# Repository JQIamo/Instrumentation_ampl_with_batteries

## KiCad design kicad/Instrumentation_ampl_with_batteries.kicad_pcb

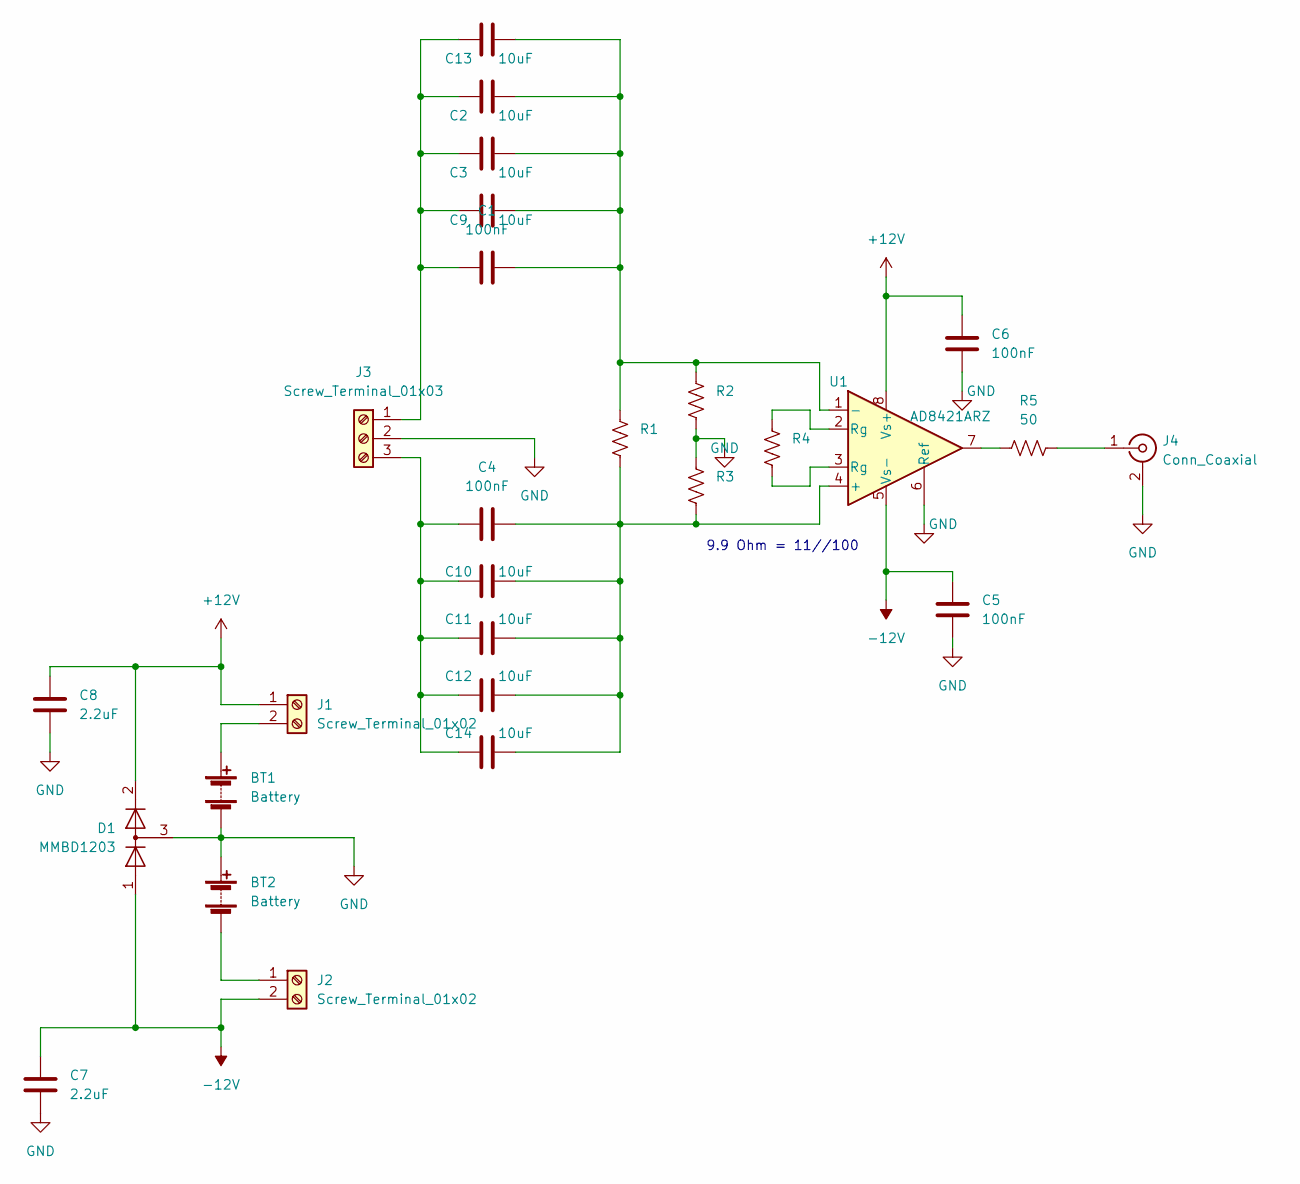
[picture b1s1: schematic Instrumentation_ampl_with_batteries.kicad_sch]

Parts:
BT1, BT2: Battery; 12V_cell_holder
C1, C4, C5, C6: 100nF; C_0603_1608Metric_Pad1.08x0.95mm_HandSolder
C2, C3, C9, C10, C11, C12, C13, C14: 10uF; C_1210_3225Metric
C7, C8: 2.2uF; C_0805_2012Metric_Pad1.18x1.45mm_HandSolder
D1: MMBD1203; SOT-23
J1, J2: Screw_Terminal_01x02; PinHeader_1x02_P2.54mm_Vertical
J3: Screw_Terminal_01x03; TerminalBlock_4Ucon_1x03_P3.50mm_Horizontal
J4: Conn_Coaxial; BNC_1cm
R1, R2, R3, R4: R_0603_1608Metric_Pad0.98x0.95mm_HandSolder
R5: 50; R_0603_1608Metric_Pad0.98x0.95mm_HandSolder
U1: AD8421ARZ; PowerIntegrations_SO-8

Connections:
+12V: C6.1, C8.1, D1.2 (A), J1.1, U1.8 (Vs+)
-12V: C5.1, C7.1, D1.1 (K), J2.2, U1.5 (Vs-)
GND: BT1.2 (-), BT2.1 (+), C5.2, C6.2, C7.2, C8.2, D1.3 (K), J3.2, J4.2 (Ext), R2.1, R3.2, U1.6 (Ref)
unnamed: BT1.1 (+), J1.2
unnamed: BT2.2 (-), J2.1
unnamed: C1.1, C2.1, C3.1, C9.1, C13.1, J3.1
unnamed: C1.2, C2.2, C3.2, C9.2, C13.2, R1.2, R2.2, U1.1 (-)
unnamed: C4.1, C10.1, C11.1, C12.1, C14.1, J3.3
unnamed: J4.1 (In), R5.2
unnamed: C4.2, C10.2, C11.2, C12.2, C14.2, R1.1, R3.1, U1.4 (+)
unnamed: R4.1, U1.3 (Rg)
unnamed: R4.2, U1.2 (Rg)
unnamed: R5.1, U1.7

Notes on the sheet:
9.9 Ohm = 11//100

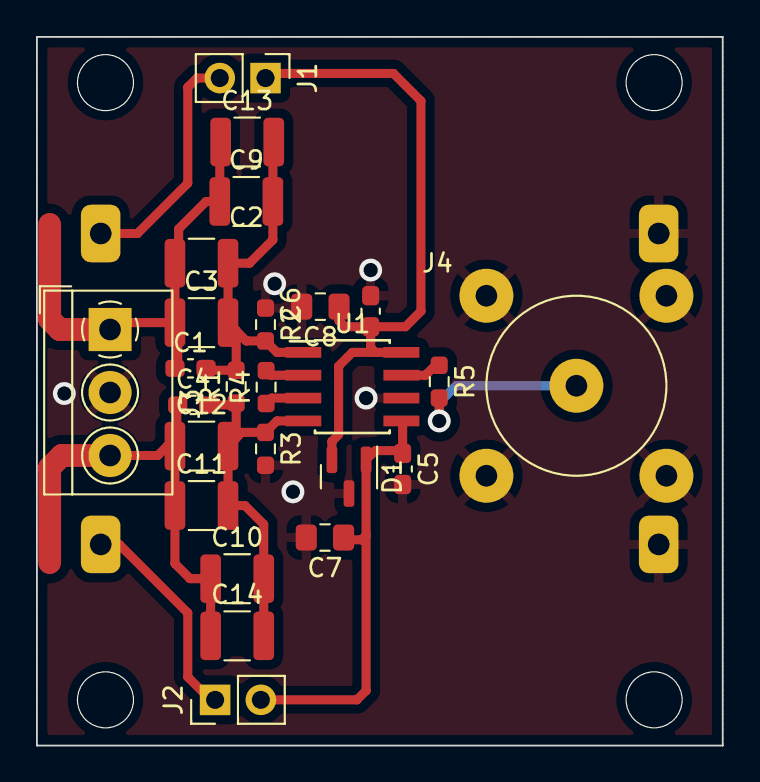
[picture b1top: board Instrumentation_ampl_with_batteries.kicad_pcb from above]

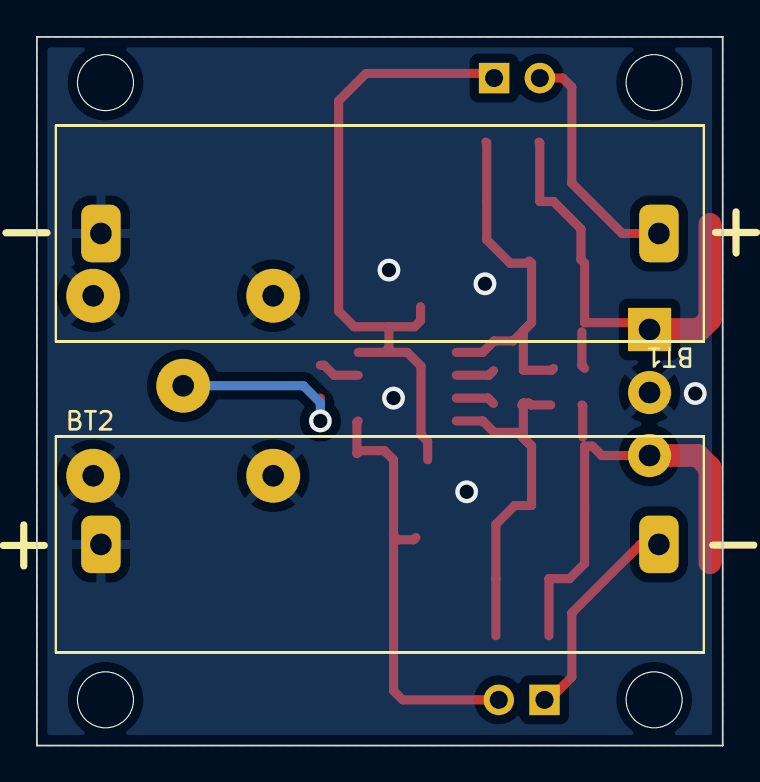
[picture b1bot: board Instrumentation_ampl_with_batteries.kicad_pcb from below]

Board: 2 copper layers, 38.1 x 39.4 mm, 27 parts (2 on the bottom side), 13 nets.

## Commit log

2023-05-05 Main files added
